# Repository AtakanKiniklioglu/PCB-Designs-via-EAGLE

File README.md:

# PCB-Designs-via-EAGLE
This repository includes PCB designs that I made via EAGLE software

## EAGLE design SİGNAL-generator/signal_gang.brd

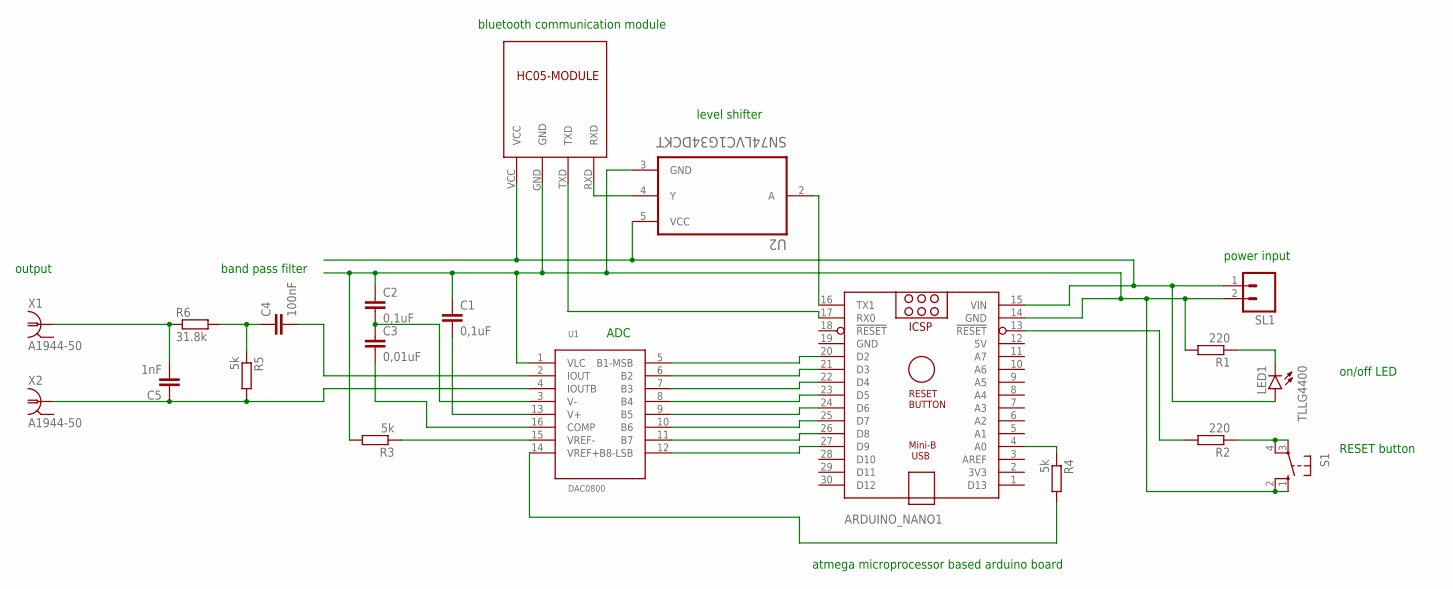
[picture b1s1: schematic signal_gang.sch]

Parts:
ARDUINO_NANO1: ARDUINO_NANO
C1, C2: 0,1uF; C2.5-2
C3: 0,01uF; C2.5-2
C4: 100nF; C2.5-2
C5: 1nF; C2.5-2
LED1: TLLG4400; LED3MM
R1, R2: 220; 0207/10
R3, R4, R5: 5k; 0207/10
R6: 31.8k; 0207/10
S1: 10-XX; B3F-10XX
SL1: M02; 02P
U1: DAC0800; DIL16
U2: SN74LVC1G34DCKT; SOT65P210X110-5N
U$1: HC05-MODULE; HC05_MODULE
X1, X2: A1944-50; A1944

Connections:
5V: ARDUINO_NANO1.12 (5V)
GND: ARDUINO_NANO1.19 (GND)
unnamed: ARDUINO_NANO1.20 (D2), U1.5 (B1-MSB)
unnamed: ARDUINO_NANO1.16 (TX1), U2.2 (A)
unnamed: ARDUINO_NANO1.4 (A0), R4.1
unnamed: ARDUINO_NANO1.21 (D3), U1.6 (B2)
unnamed: ARDUINO_NANO1.22 (D4), U1.7 (B3)
unnamed: ARDUINO_NANO1.23 (D5), U1.8 (B4)
unnamed: ARDUINO_NANO1.24 (D6), U1.9 (B5)
unnamed: ARDUINO_NANO1.25 (D7), U1.10 (B6)
unnamed: ARDUINO_NANO1.26 (D8), U1.11 (B7)
unnamed: ARDUINO_NANO1.27 (D9), U1.12 (B8-LSB)
unnamed: C5.1, R5.2, U1.4 (IOUTB), X2.1
unnamed: ARDUINO_NANO1.17 (RX0), U$1.TXD
unnamed: ARDUINO_NANO1.15 (VIN), LED1.A, SL1.1, U2.5 (VCC), U$1.VCC
unnamed: U2.4 (Y), U$1.RXD
unnamed: LED1.K (C), R1.1
unnamed: C4.1, R5.1, R6.2
unnamed: ARDUINO_NANO1.13 (!RESET), R2.2
unnamed: R2.1, S1.3, S1.4 (P1)
unnamed: ARDUINO_NANO1.14 (GND), C1.1, C2.1, R1.2, R3.2, S1.1 (S), S1.2 (S1), SL1.2, U1.1 (VLC), U2.3 (GND), U$1.GND
unnamed: R3.1, U1.15 (VREF-)
unnamed: C1.2, U1.13 (V+)
unnamed: C3.2, U1.16 (COMP)
unnamed: C2.2, C3.1, U1.3 (V-)
unnamed: C4.2, U1.2 (IOUT)
unnamed: R4.2, U1.14 (VREF+)
unnamed: C5.2, R6.1, X1.1

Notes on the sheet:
power input
output
band pass filter
ADC
atmega microprocessor based arduino board
level shifter
bluetooth communication module
on/off LED
RESET button

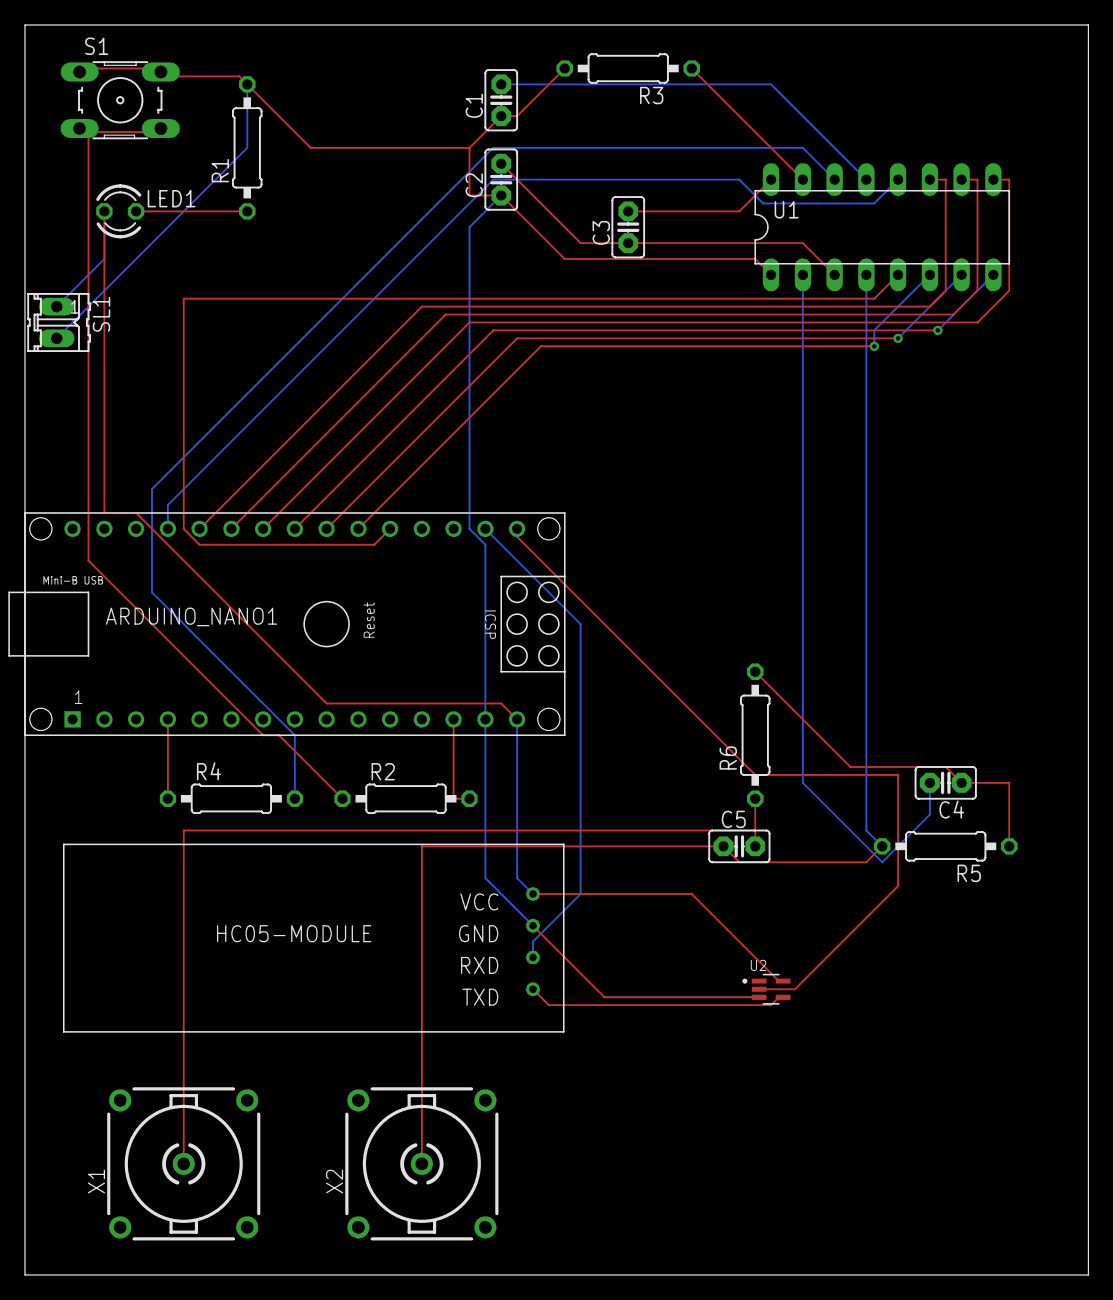
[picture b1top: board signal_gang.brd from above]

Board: 2 copper layers, 85.1 x 100.0 mm, 20 parts (0 on the bottom side), 26 nets.

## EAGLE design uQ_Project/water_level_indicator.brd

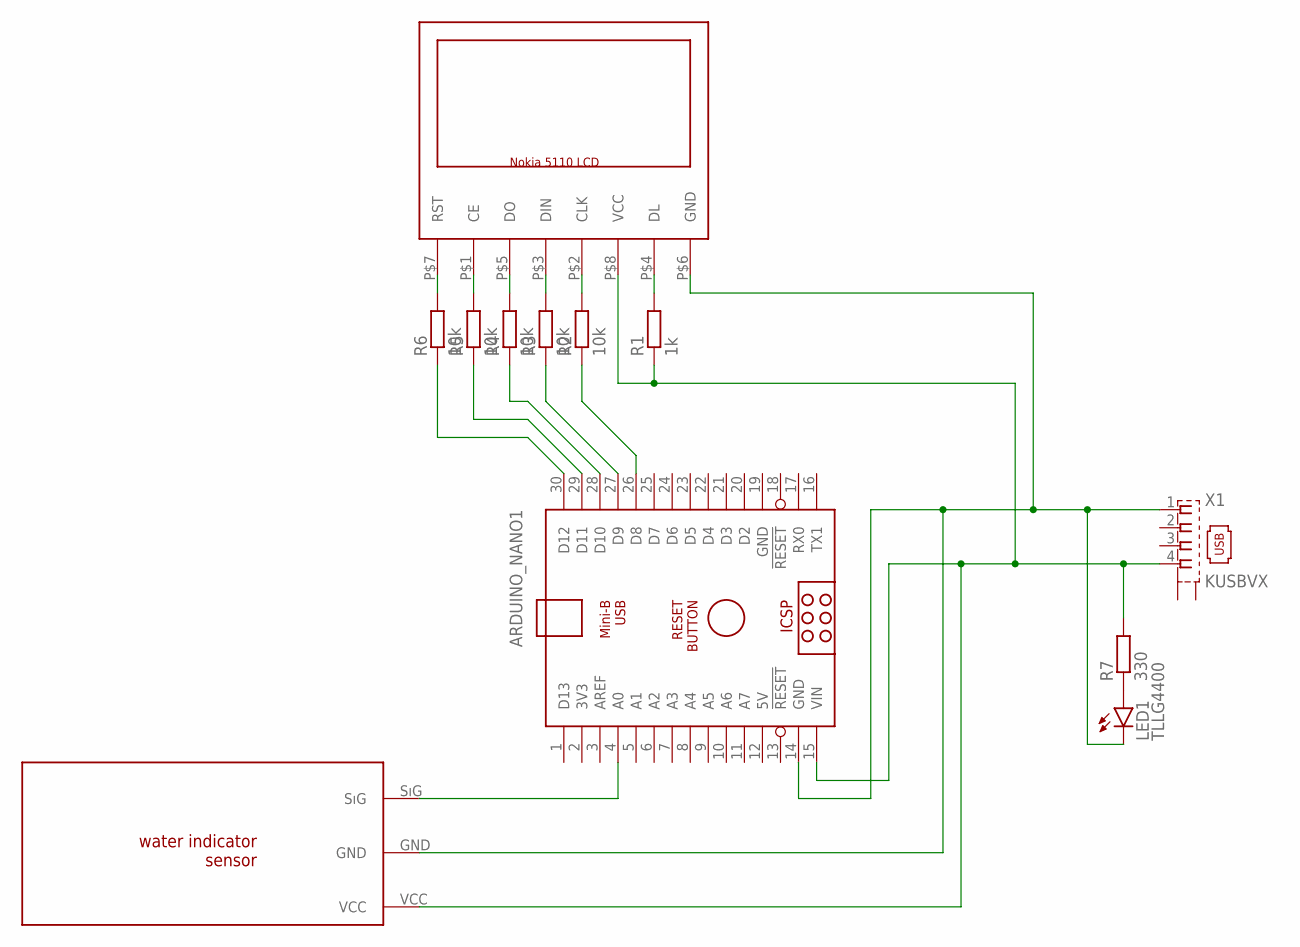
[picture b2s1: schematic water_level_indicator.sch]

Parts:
ARDUINO_NANO1: ARDUINO_NANO
LED1: TLLG4400; LED3MM
R1: 1k; 0207/10
R2, R3, R4, R5, R6: 10k; 0207/10
R7: 330; 0207/10
U$1: WATER_LEVEL_IND
U$2: NOKİA5110LCD
X1: KUSBVX

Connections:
5V: ARDUINO_NANO1.12 (5V)
GND: ARDUINO_NANO1.19 (GND)
unnamed: ARDUINO_NANO1.15 (VIN), R1.1, R7.2, U$1.VCC, U$2.P$8 (VCC), X1.4
unnamed: ARDUINO_NANO1.14 (GND), LED1.K (C), U$1.GND, U$2.P$6 (GND), X1.1
unnamed: ARDUINO_NANO1.4 (A0), U$1.SıG
unnamed: R1.2, U$2.P$4 (DL)
unnamed: R2.2, U$2.P$2 (CLK)
unnamed: R3.2, U$2.P$3 (DIN)
unnamed: R4.2, U$2.P$5 (DO)
unnamed: R5.2, U$2.P$1 (CE)
unnamed: R6.2, U$2.P$7 (RST)
unnamed: ARDUINO_NANO1.26 (D8), R2.1
unnamed: ARDUINO_NANO1.27 (D9), R3.1
unnamed: ARDUINO_NANO1.28 (D10), R4.1
unnamed: ARDUINO_NANO1.29 (D11), R5.1
unnamed: ARDUINO_NANO1.30 (D12), R6.1
unnamed: LED1.A, R7.1

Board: 2 copper layers, 12 parts (0 on the bottom side), 15 nets, no tracks yet.

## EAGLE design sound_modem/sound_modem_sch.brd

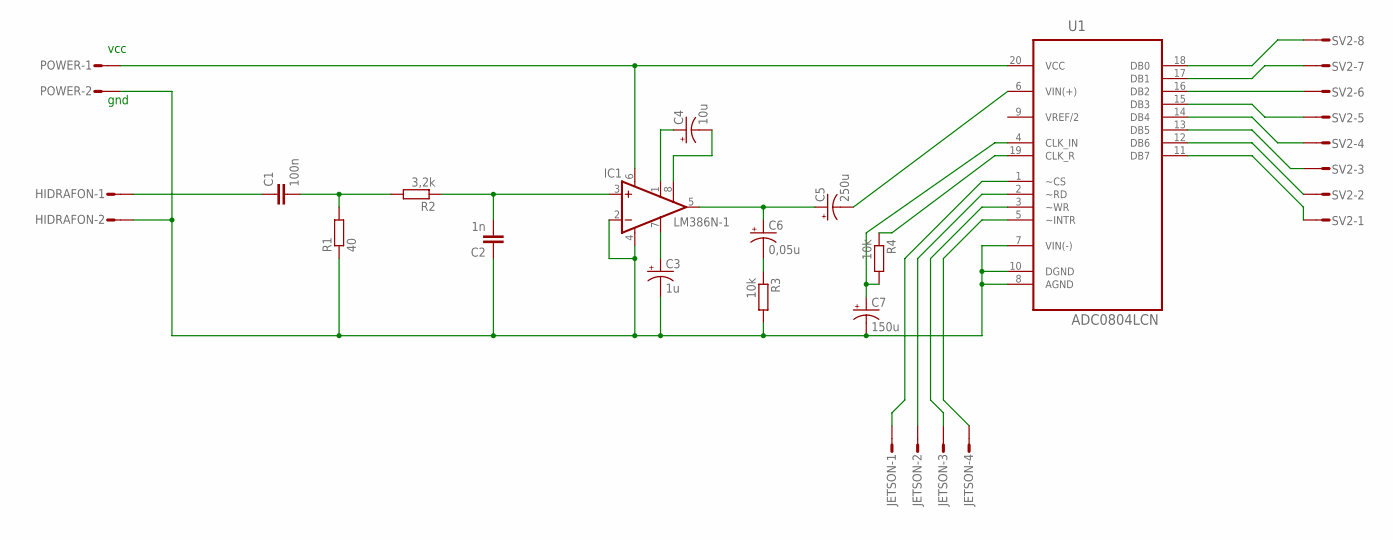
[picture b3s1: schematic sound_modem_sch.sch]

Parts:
C1: 100n; C025-025X050
C2: 1n; C025-025X050
C3: 1u; E2-5
C4: 10u; E2-5
C5: 250u; E5-10,5
C6: 0,05u; E2-5
C7: 150u; E5-10,5
HIDRAFON: L02P
IC1: LM386N-1; DIL08
JETSON: L04P
POWER: L02P
R1: 40; 0204/7
R2: 3,2k; 0204/7
R3, R4: 10k; 0204/7
SV2: L08P
U1: ADC0804LCN; DIP254P762X508-20

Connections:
unnamed: C1.1, HIDRAFON.1
unnamed: C1.2, R1.2, R2.2
unnamed: C2.2, IC1.3 (+IN), R2.1
unnamed: C2.1, C3.-, C7.-, HIDRAFON.2, IC1.2 (-IN), IC1.4 (GND), POWER.2, R1.1, R3.2, U1.7 (VIN(-)), U1.8 (AGND), U1.10 (DGND)
unnamed: C3.+, IC1.7 (BYPASS)
unnamed: R4.1, U1.19 (CLK_R)
unnamed: IC1.6 (VS), POWER.1, U1.20 (VCC)
unnamed: C4.+, IC1.1 (GAIN)
unnamed: C4.-, IC1.8 (GAIN)
unnamed: C5.+, C6.+, IC1.5 (OUT)
unnamed: C6.-, R3.1
unnamed: C7.+, R4.2, U1.4 (CLK_IN)
unnamed: C5.-, U1.6 (VIN(+))
unnamed: JETSON.1, U1.1 (~CS)
unnamed: JETSON.2, U1.2 (~RD)
unnamed: JETSON.3, U1.3 (~WR)
unnamed: JETSON.4, U1.5 (~INTR)
unnamed: SV2.8, U1.18 (DB0)
unnamed: SV2.7, U1.17 (DB1)
unnamed: SV2.6, U1.16 (DB2)
unnamed: SV2.5, U1.15 (DB3)
unnamed: SV2.4, U1.14 (DB4)
unnamed: SV2.3, U1.13 (DB5)
unnamed: SV2.2, U1.12 (DB6)
unnamed: SV2.1, U1.11 (DB7)

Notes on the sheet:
vcc
gnd

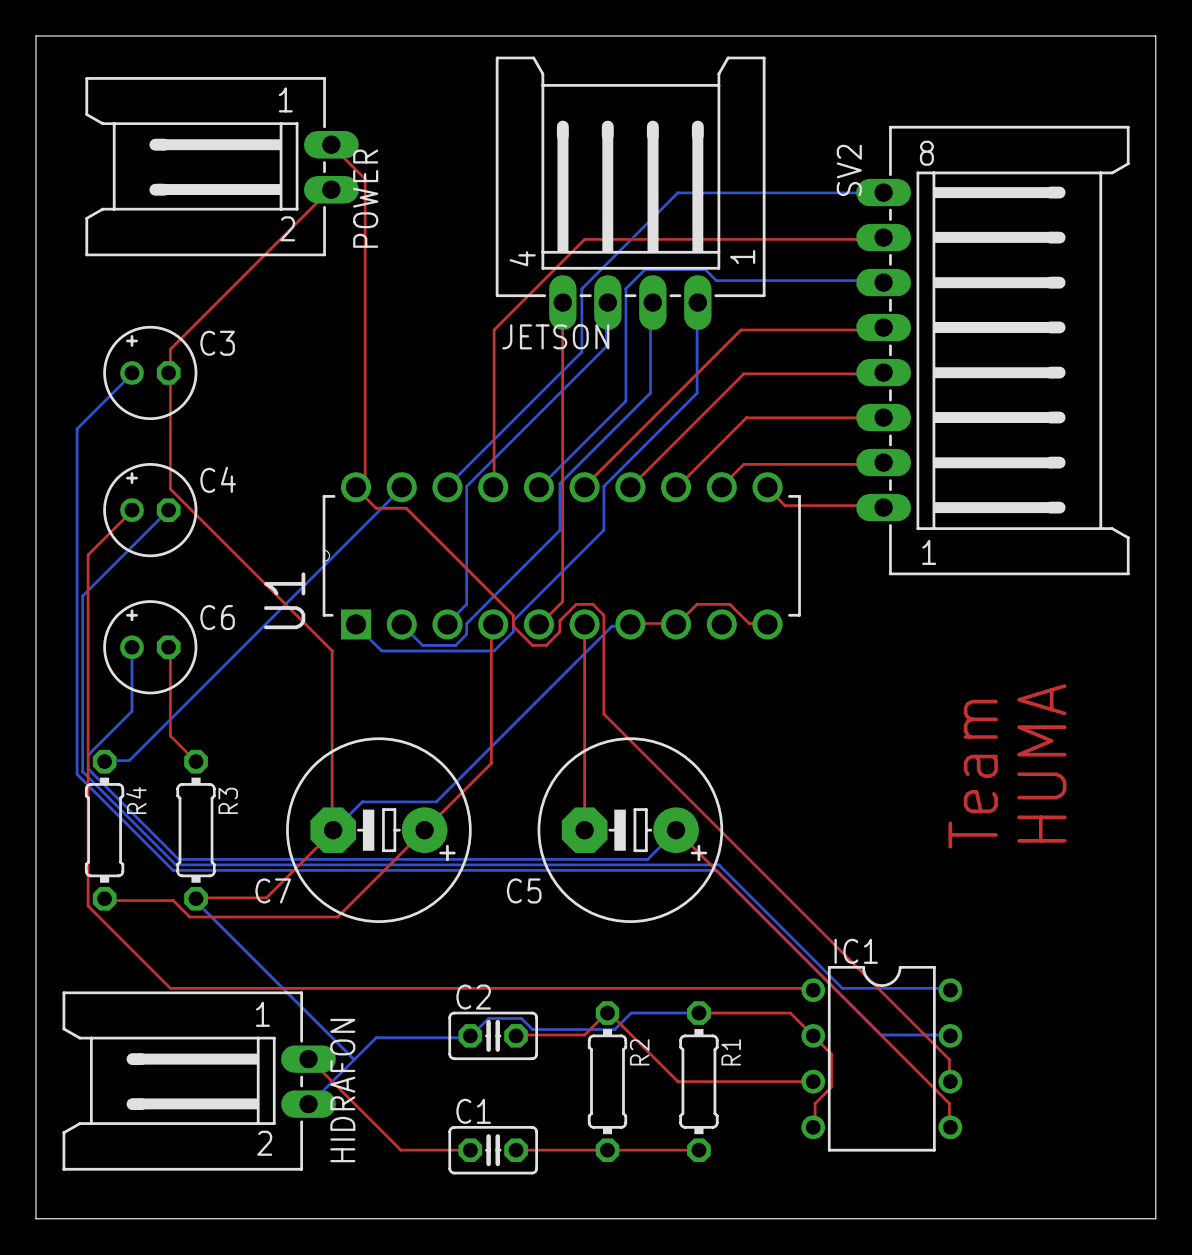
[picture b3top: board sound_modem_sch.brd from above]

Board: 2 copper layers, 62.2 x 65.7 mm, 17 parts (0 on the bottom side), 25 nets.

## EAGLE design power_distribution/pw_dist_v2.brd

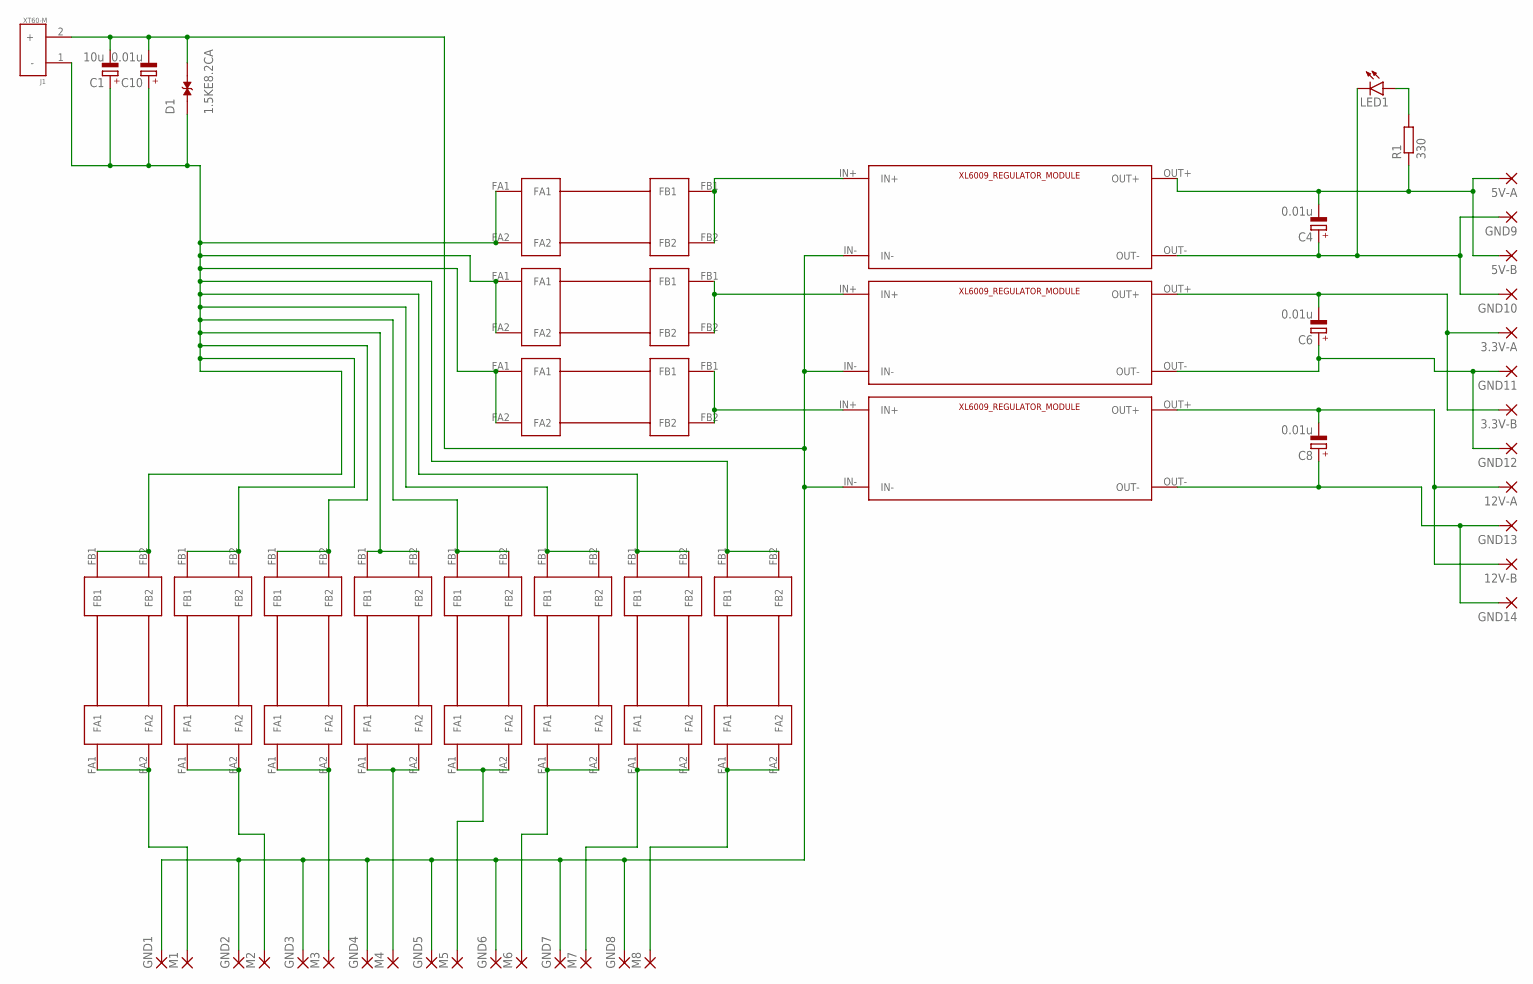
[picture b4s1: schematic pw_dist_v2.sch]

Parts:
3.3V-A, 3.3V-B, 5V-A, 5V-B, 12V-A, 12V-B: SMD5; SMD2,54-5,08
C1: 10u; E5-10,5
C4, C6, C8, C10: 0.01u; E5-10,5
D1: 1.5KE8.2CA; DIOAD1586W101L900D530
GND1, GND2, GND3, GND4, GND5, GND6, GND7, GND8, GND9, GND10, GND11, GND12, GND13, GND14: SMD5; SMD2,54-5,08
J1: XT60-M; AMASS_XT60-M
LED1: LED5MM
M1, M2, M3, M4, M5, M6, M7, M8: SMD5; SMD2,54-5,08
R1: 330; 0207/10
U$1, U$2, U$3: XL6009_MODULE
U$4, U$5, U$6, U$7, U$8, U$9, U$10, U$11, U$12, U$13, U$14: FUSE_HOLDER_2

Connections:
unnamed: U$2.IN+, U$4.FB1, U$4.FB2
unnamed: U$1.IN+, U$5.FB1, U$5.FB2
unnamed: U$3.IN+, U$6.FB1, U$6.FB2
unnamed: C1.-, C10.-, D1.2, GND1.1, GND2.1, GND3.1, GND4.1, GND5.1, GND6.1, GND7.1, GND8.1, J1.2 (+), U$1.IN-, U$2.IN-, U$3.IN-
unnamed: M1.1, U$14.FA1, U$14.FA2
unnamed: M2.1, U$13.FA1, U$13.FA2
unnamed: M3.1, U$12.FA1, U$12.FA2
unnamed: M4.1, U$11.FA1, U$11.FA2
unnamed: M5.1, U$10.FA1, U$10.FA2
unnamed: M6.1, U$9.FA1, U$9.FA2
unnamed: M7.1, U$8.FA1, U$8.FA2
unnamed: C1.+, C10.+, D1.1, J1.1 (-), U$4.FA1, U$4.FA2, U$5.FA1, U$5.FA2, U$6.FA1, U$6.FA2, U$7.FB1, U$7.FB2, U$8.FB1, U$8.FB2, U$9.FB1, U$9.FB2, U$10.FB1, U$10.FB2, U$11.FB1, U$11.FB2, U$12.FB1, U$12.FB2, U$13.FB1, U$13.FB2, U$14.FB1, U$14.FB2
unnamed: M8.1, U$7.FA1, U$7.FA2
unnamed: 5V-A.1, 5V-B.1, C4.-, R1.1, U$2.OUT+
unnamed: C4.+, GND9.1, GND10.1, LED1.K (C), U$2.OUT-
unnamed: 3.3V-A.1, 3.3V-B.1, C6.-, U$1.OUT+
unnamed: C6.+, GND11.1, GND12.1, U$1.OUT-
unnamed: 12V-A.1, 12V-B.1, C8.-, U$3.OUT+
unnamed: C8.+, GND13.1, GND14.1, U$3.OUT-
unnamed: LED1.A, R1.2

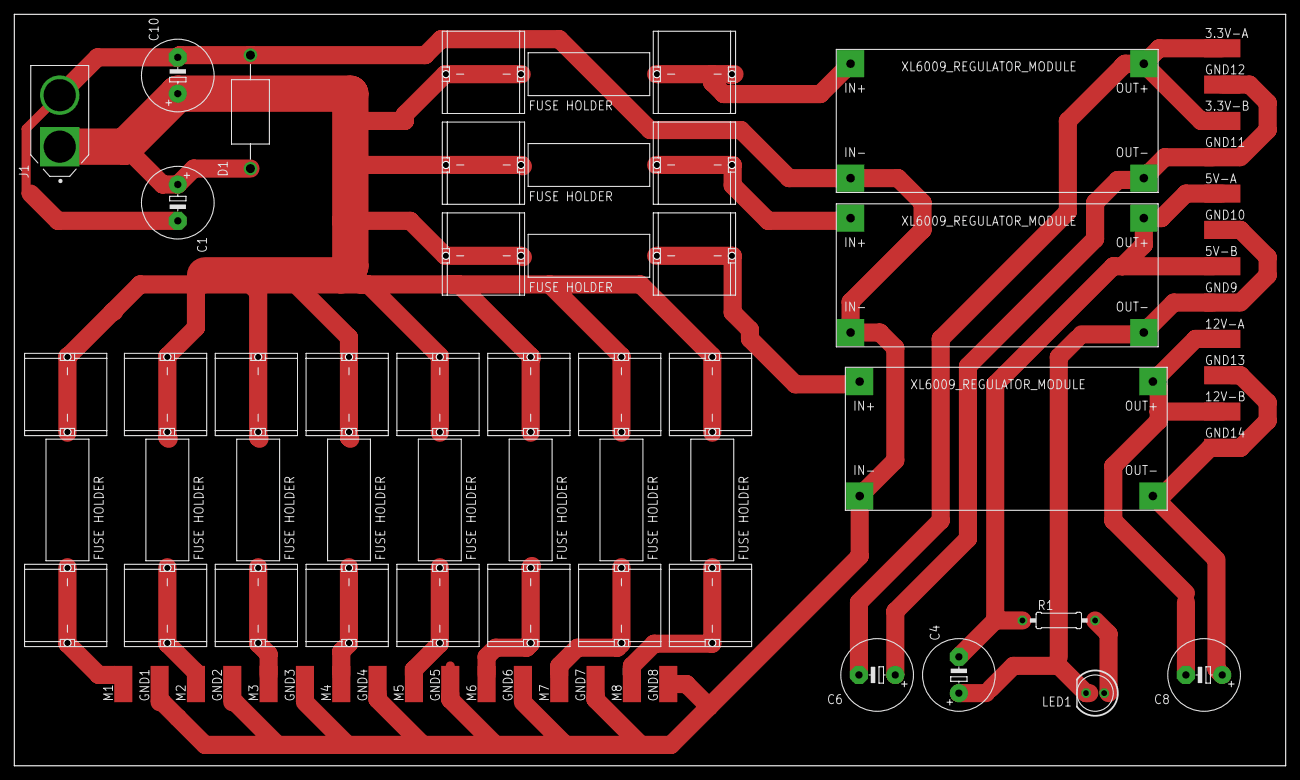
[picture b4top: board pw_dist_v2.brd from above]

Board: 2 copper layers, 177.8 x 105.1 mm, 51 parts (0 on the bottom side), 20 nets.

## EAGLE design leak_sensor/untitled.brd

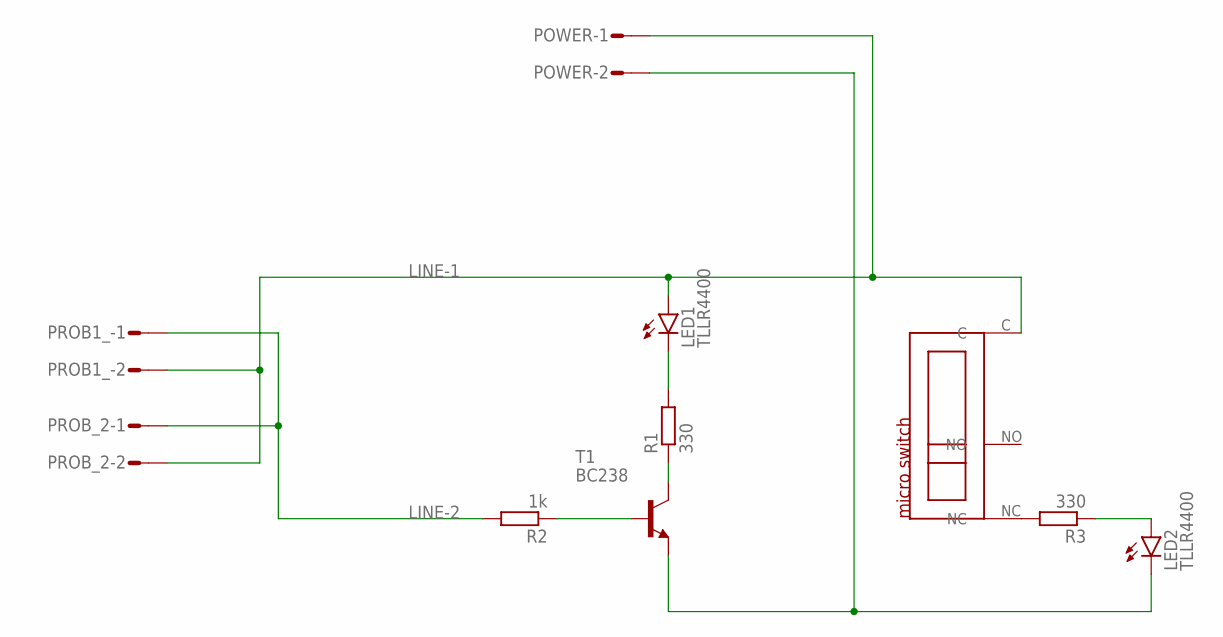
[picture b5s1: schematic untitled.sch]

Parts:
LED1, LED2: TLLR4400; LED3MM
POWER: L02P
PROB1_: L02P
PROB_2: L02P
R1, R3: 330; 0204/7
R2: 1k; 0204/7
T1: BC238; TO92
U$1: MICRO_SWITCH

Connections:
LINE-1: LED1.A, POWER.1, PROB1_.2, PROB_2.2, U$1.C
LINE-2: PROB1_.1, PROB_2.1, R2.2
unnamed: R2.1, T1.2 (B)
unnamed: R1.1, T1.3 (C)
unnamed: LED2.K (C), POWER.2, T1.1 (E)
unnamed: LED1.K (C), R1.2
unnamed: R3.2, U$1.NC
unnamed: LED2.A, R3.1

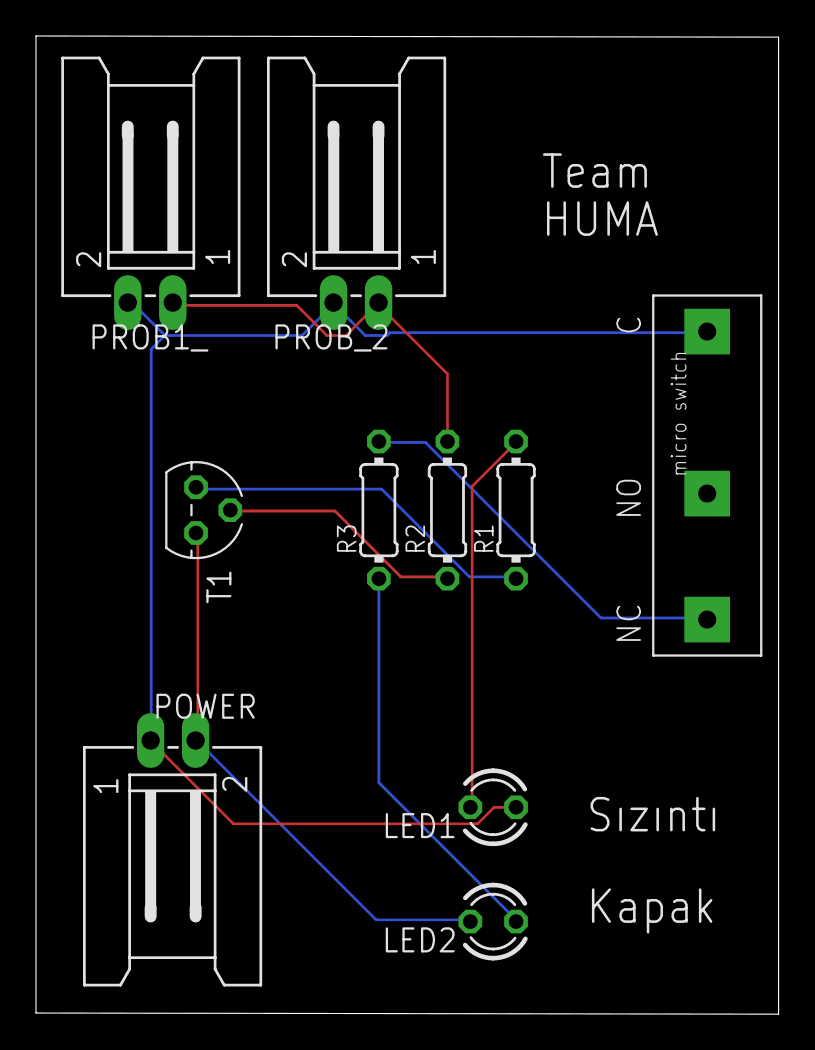
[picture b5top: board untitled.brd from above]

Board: 2 copper layers, 41.3 x 54.3 mm, 10 parts (0 on the bottom side), 8 nets.

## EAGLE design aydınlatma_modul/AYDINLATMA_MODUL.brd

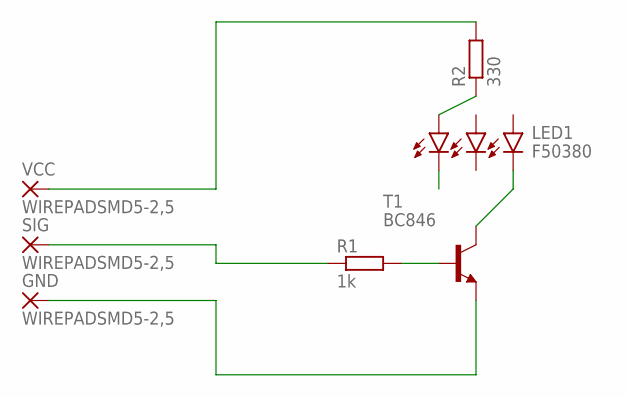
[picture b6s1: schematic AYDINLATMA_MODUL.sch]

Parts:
GND: WIREPADSMD5-2,5; 5-2,5
LED1: F50380
R1: 1k; R0805
R2: 330; R0805
SIG: WIREPADSMD5-2,5; 5-2,5
T1: BC846; SOT23
VCC: WIREPADSMD5-2,5; 5-2,5

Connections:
unnamed: R1.2, T1.1 (B)
unnamed: LED1.R-, T1.3 (C)
unnamed: GND.1, T1.2 (E)
unnamed: LED1.B+, R2.1
unnamed: R1.1, SIG.1
unnamed: R2.2, VCC.1

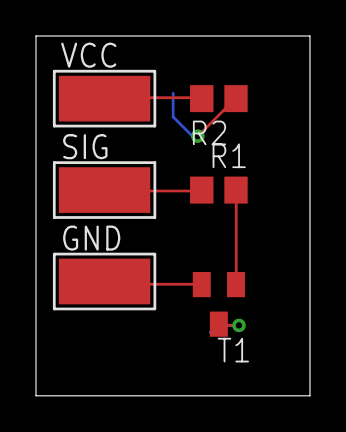
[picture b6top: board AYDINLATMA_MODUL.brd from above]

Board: 2 copper layers, 15.2 x 20.0 mm, 7 parts (1 on the bottom side), 6 nets.

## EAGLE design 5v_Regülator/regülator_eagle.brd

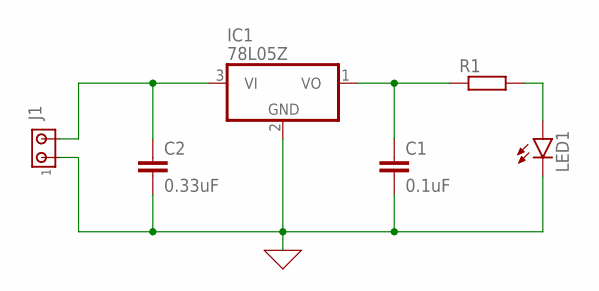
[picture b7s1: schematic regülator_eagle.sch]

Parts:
C1: 0.1uF; C2.5-3
C2: 0.33uF; C2.5-3
IC1: 78L05Z; TO92
J1: MTA02-100; 10X02MTA
LED1: LED5MM
R1: R-EU_0207/10; 0207/10

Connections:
0: C1.2, C2.2, IC1.2 (GND), J1.1, LED1.K (C)
unnamed: C1.1, IC1.1 (VO), R1.1
unnamed: LED1.A, R1.2
unnamed: C2.1, IC1.3 (VI), J1.2

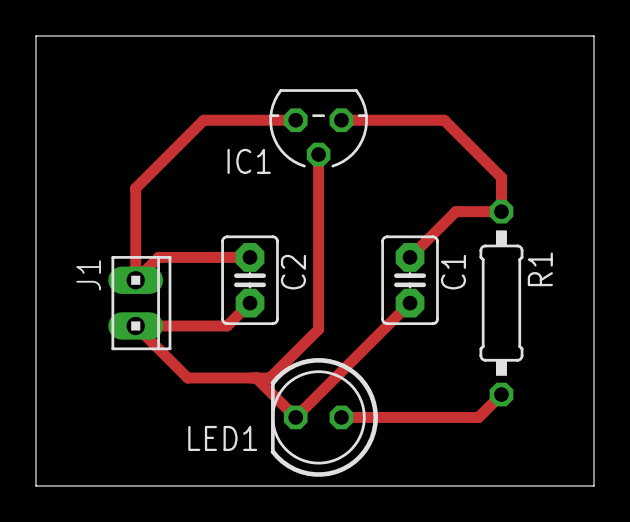
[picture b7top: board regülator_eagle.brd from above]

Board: 2 copper layers, 31.0 x 25.0 mm, 6 parts (0 on the bottom side), 4 nets.
